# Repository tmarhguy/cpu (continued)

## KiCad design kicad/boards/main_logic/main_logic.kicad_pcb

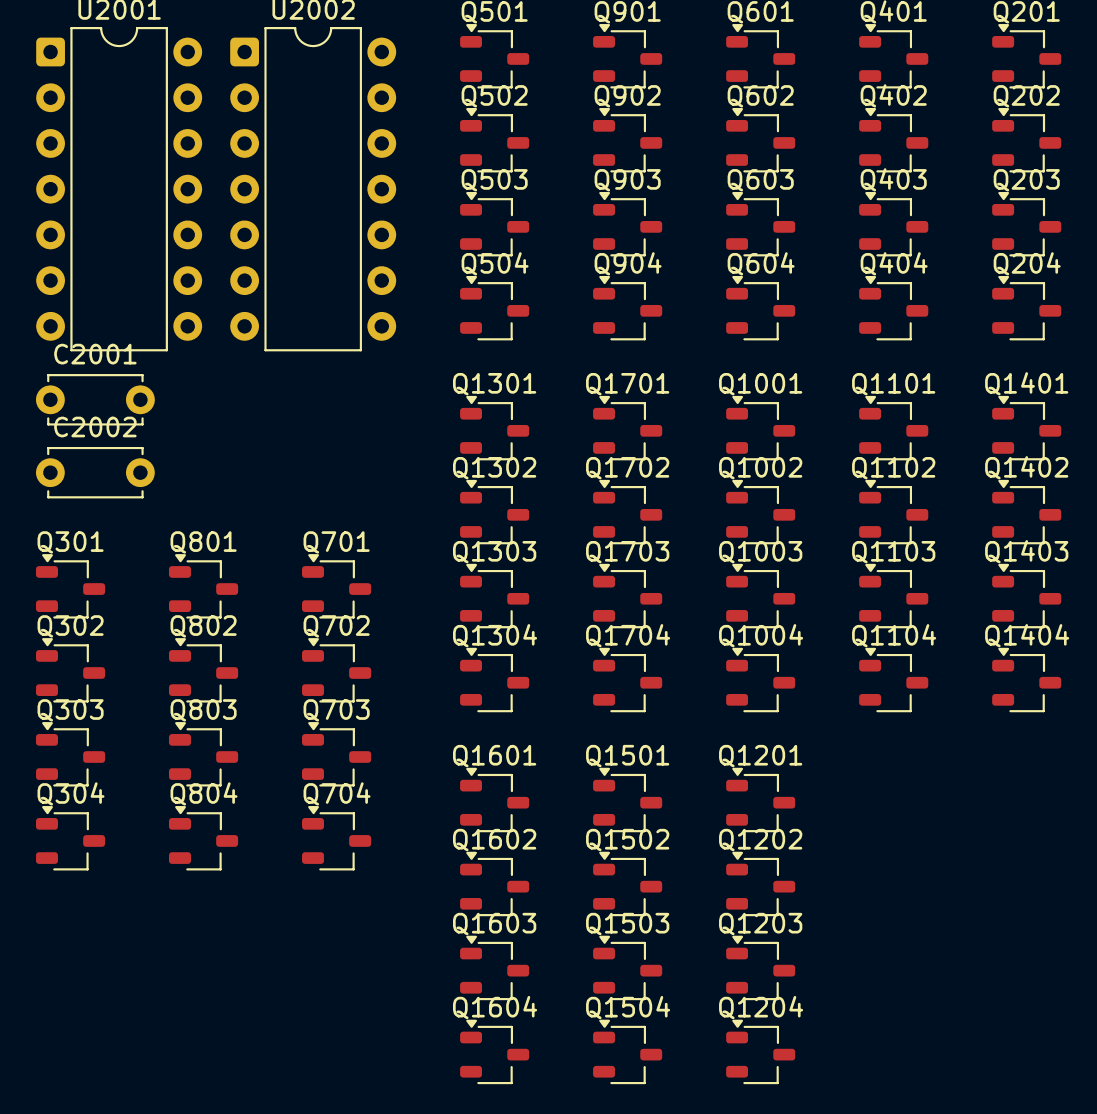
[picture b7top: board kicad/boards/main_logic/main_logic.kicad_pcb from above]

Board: 2 copper layers, 68 parts (0 on the bottom side), 66 nets, no tracks yet.

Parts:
C2001, C2002: 100nF; C_Disc_D5.0mm_W2.5mm_P5.00mm
Q201, Q204, Q301, Q304, Q401, Q404, Q501, Q504, Q601, Q604, Q701, Q704, Q801, Q804, Q901, Q904, Q1002, Q1003, Q1102, Q1103, Q1202, Q1203, Q1302, Q1303, Q1402, Q1403, Q1502, Q1503, Q1602, Q1603, Q1702, Q1703: PMOS; TSOT-23
Q202, Q203, Q302, Q303, Q402, Q403, Q502, Q503, Q602, Q603, Q702, Q703, Q802, Q803, Q902, Q903, Q1001, Q1004, Q1101, Q1104, Q1201, Q1204, Q1301, Q1304, Q1401, Q1404, Q1501, Q1504, Q1601, Q1604, Q1701, Q1704: NMOS; TSOT-23
U2001, U2002: 74HC86; DIP-14_W7.62mm

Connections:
/nand8_1/A0: Q201.2 (G), Q203.2 (G)
/nand8_1/A1: Q301.2 (G), Q303.2 (G)
/nand8_1/A2: Q401.2 (G), Q403.2 (G)
/nand8_1/A3: Q501.2 (G), Q503.2 (G)
/nand8_1/A4: Q601.2 (G), Q603.2 (G)
/nand8_1/A5: Q701.2 (G), Q703.2 (G)
/nand8_1/A6: Q801.2 (G), Q803.2 (G)
/nand8_1/A7: Q901.2 (G), Q903.2 (G)
/nand8_1/B0: Q202.2 (G), Q204.2 (G)
/nand8_1/B1: Q302.2 (G), Q304.2 (G)
/nand8_1/B2: Q402.2 (G), Q404.2 (G)
/nand8_1/B3: Q502.2 (G), Q504.2 (G)
/nand8_1/B4: Q602.2 (G), Q604.2 (G)
/nand8_1/B5: Q702.2 (G), Q704.2 (G)
/nand8_1/B6: Q802.2 (G), Q804.2 (G)
/nand8_1/B7: Q902.2 (G), Q904.2 (G)
/nand8_1/Y0: Q201.1 (D), Q202.1 (D), Q204.1 (D)
/nand8_1/Y1: Q301.1 (D), Q302.1 (D), Q304.1 (D)
/nand8_1/Y2: Q401.1 (D), Q402.1 (D), Q404.1 (D)
/nand8_1/Y3: Q501.1 (D), Q502.1 (D), Q504.1 (D)
/nand8_1/Y4: Q601.1 (D), Q602.1 (D), Q604.1 (D)
/nand8_1/Y5: Q701.1 (D), Q702.1 (D), Q704.1 (D)
/nand8_1/Y6: Q801.1 (D), Q802.1 (D), Q804.1 (D)
/nand8_1/Y7: Q901.1 (D), Q902.1 (D), Q904.1 (D)
/nor8_1/A0: Q1001.2 (G), Q1002.2 (G)
/nor8_1/A1: Q1101.2 (G), Q1102.2 (G)
/nor8_1/A2: Q1201.2 (G), Q1202.2 (G)
/nor8_1/A3: Q1301.2 (G), Q1302.2 (G)
/nor8_1/A4: Q1401.2 (G), Q1402.2 (G)
/nor8_1/A5: Q1501.2 (G), Q1502.2 (G)
/nor8_1/A6: Q1601.2 (G), Q1602.2 (G)
/nor8_1/A7: Q1701.2 (G), Q1702.2 (G)
/nor8_1/B0: Q1003.2 (G), Q1004.2 (G)
/nor8_1/B1: Q1103.2 (G), Q1104.2 (G)
/nor8_1/B2: Q1203.2 (G), Q1204.2 (G)
/nor8_1/B3: Q1303.2 (G), Q1304.2 (G)
/nor8_1/B4: Q1403.2 (G), Q1404.2 (G)
/nor8_1/B5: Q1503.2 (G), Q1504.2 (G)
/nor8_1/B6: Q1603.2 (G), Q1604.2 (G)
/nor8_1/B7: Q1703.2 (G), Q1704.2 (G)
/nor8_1/Y0: Q1001.1 (D), Q1003.1 (D), Q1004.1 (D)
/nor8_1/Y1: Q1101.1 (D), Q1103.1 (D), Q1104.1 (D)
/nor8_1/Y2: Q1201.1 (D), Q1203.1 (D), Q1204.1 (D)
/nor8_1/Y3: Q1301.1 (D), Q1303.1 (D), Q1304.1 (D)
/nor8_1/Y4: Q1401.1 (D), Q1403.1 (D), Q1404.1 (D)
/nor8_1/Y5: Q1501.1 (D), Q1503.1 (D), Q1504.1 (D)
/nor8_1/Y6: Q1601.1 (D), Q1603.1 (D), Q1604.1 (D)
/nor8_1/Y7: Q1701.1 (D), Q1703.1 (D), Q1704.1 (D)
GND: C2001.2, C2002.2, Q203.3 (S), Q303.3 (S), Q403.3 (S), Q503.3 (S), Q603.3 (S), Q703.3 (S), Q803.3 (S), Q903.3 (S), Q1001.3 (S), Q1004.3 (S), Q1101.3 (S), Q1104.3 (S), Q1201.3 (S), Q1204.3 (S), Q1301.3 (S), Q1304.3 (S), Q1401.3 (S), Q1404.3 (S), Q1501.3 (S), Q1504.3 (S), Q1601.3 (S), Q1604.3 (S), Q1701.3 (S), Q1704.3 (S), U2001.7 (GND), U2002.7 (GND)
unnamed: Q202.3 (S), Q203.1 (D)
unnamed: Q302.3 (S), Q303.1 (D)
unnamed: Q402.3 (S), Q403.1 (D)
unnamed: Q502.3 (S), Q503.1 (D)
unnamed: Q602.3 (S), Q603.1 (D)
unnamed: Q702.3 (S), Q703.1 (D)
unnamed: Q802.3 (S), Q803.1 (D)
unnamed: Q902.3 (S), Q903.1 (D)
unnamed: Q1002.1 (D), Q1003.3 (S)
unnamed: Q1102.1 (D), Q1103.3 (S)
unnamed: Q1202.1 (D), Q1203.3 (S)
unnamed: Q1302.1 (D), Q1303.3 (S)
unnamed: Q1402.1 (D), Q1403.3 (S)
unnamed: Q1502.1 (D), Q1503.3 (S)
unnamed: Q1602.1 (D), Q1603.3 (S)
unnamed: Q1702.1 (D), Q1703.3 (S)
VCC: C2001.1, C2002.1, Q201.3 (S), Q204.3 (S), Q301.3 (S), Q304.3 (S), Q401.3 (S), Q404.3 (S), Q501.3 (S), Q504.3 (S), Q601.3 (S), Q604.3 (S), Q701.3 (S), Q704.3 (S), Q801.3 (S), Q804.3 (S), Q901.3 (S), Q904.3 (S), Q1002.3 (S), Q1102.3 (S), Q1202.3 (S), Q1302.3 (S), Q1402.3 (S), Q1502.3 (S), Q1602.3 (S), Q1702.3 (S), U2001.14 (VCC), U2002.14 (VCC)

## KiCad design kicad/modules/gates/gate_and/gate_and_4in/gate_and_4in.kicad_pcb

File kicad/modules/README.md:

# KiCad Modules

This directory contains individual circuit modules organized by component type and specifications.

## Directory Structure

The modules are organized to match the component inventory requirements:

### Gate Modules

#### AND Gates
- `gate_and/gate_and_2in/` - 2-input, 1-bit AND gates (10× used in ALU)
- `gate_and/gate_and_3in/` - 3-input, 1-bit AND gates (1× used in ALU)
- `gate_and/gate_and_4in/` - 4-input, 1-bit AND gates (19× used in ALU - most common)
- `gate_and_8bit/` - 8-bit wide AND gates (legacy/alternative)

#### OR Gates
- `gate_or/gate_or_2in/` - 2-input, 1-bit OR gates (7× used in ALU)
- `gate_or/gate_or_3in/` - 3-input, 1-bit OR gates (1× used in ALU)
- `gate_or_8bit/` - 8-bit wide OR gates (legacy/alternative)

#### NOT Gates (Inverters)
- `gate_inv/gate_inv_1bit/` - 1-bit inverters (40× used in ALU)
- `gate_inv/gate_inv_8bit/` - 8-bit wide inverters (1× used in ALU)

#### NAND Gates
- `gate_nand/gate_nand_2in_8bit/` - 2-input, 8-bit NAND (1× used in ALU)
- `gate_nand/` - Legacy NAND gates

#### NOR Gates
- `gate_nor/gate_nor_2in_1bit/` - 2-input, 1-bit NOR (1× used in ALU)
- `gate_nor/gate_nor_2in_8bit/` - 2-input, 8-bit NOR (1× used in ALU)
- `gate_nor/gate_nor_8in_1bit/` - 8-input, 1-bit NOR for zero detection (1× used in ALU)
- `gate_nor_8bit/` - Legacy NOR gates

#### XOR Gates
- `gate_xor/gate_xor_2in_8bit/` - 2-input, 8-bit XOR (3× used in ALU)
- `gate_xor/` - Legacy XOR gates
- `gate_xor_8bit/` - Alternative 8-bit XOR
- `gate_xor_ic/` - XOR implemented as IC (74HC86)

#### XNOR Gates
- `gate_xnor/` - XNOR gate modules

### Multiplexers

#### MUX Modules
- `mux/mux_2to1_8bit/` - 2:1 MUX, 1-bit select, 8-bit data (2× used in ALU)
- `mux/mux_4to1_8bit/` - 4:1 MUX, 2-bit select, 8-bit data (3× used in ALU)
- `mux/mux_8to1_8bit/` - 8:1 MUX, 3-bit select, 8-bit data (1× used in ALU)
- `mux_8bit/` - Legacy multiplexer modules

### Arithmetic Modules

- `adder1/` - Single-bit full adder
- `adder2/` - 2-bit full adder
- `adder8/` - 8-bit full adder

### ALU Core

- `alu_core/` - ALU core module integration

## Usage Notes

1. **Primary Modules:** Use the organized subdirectories (e.g., `gate_and/gate_and_4in/`) for new designs matching the component inventory.

2. **Legacy Modules:** The root-level directories (e.g., `gate_and/`, `gate_or_8bit/`) contain existing designs and are preserved for compatibility.

3. **Component Sizes:** The organization matches the exact component sizes used in the ALU top circuit as documented in `docs/build-notes/component_inventory.md`.

4. **File Naming:** Each module directory should contain:
   - `.kicad_sch` - Schematic file
   - `.kicad_pcb` - PCB layout file
   - `.kicad_pro` - Project file
   - Backup subdirectories
   - Related documentation

## Migration Notes

When organizing existing designs:
- Move 2-input AND gates → `gate_and/gate_and_2in/`
- Move 3-input AND gates → `gate_and/gate_and_3in/`
- Move 4-input AND gates → `gate_and/gate_and_4in/`
- Move 2-input OR gates → `gate_or/gate_or_2in/`
- Move 3-input OR gates → `gate_or/gate_or_3in/`
- Move 1-bit inverters → `gate_inv/gate_inv_1bit/`
- Move 8-bit inverters → `gate_inv/gate_inv_8bit/`
- Move multiplexers by size → `mux/mux_*to1_8bit/`

---

*Last updated: 2026-01-08*

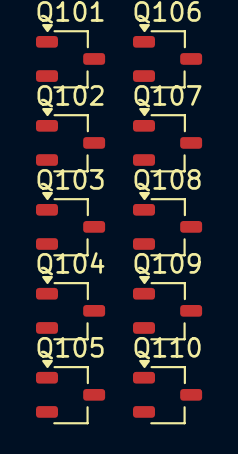
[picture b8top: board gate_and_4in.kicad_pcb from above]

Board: 2 copper layers, 10 parts (0 on the bottom side), 11 nets, no tracks yet.

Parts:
Q101, Q106, Q107, Q108, Q109: PMOS; TSOT-23
Q102, Q103, Q104, Q105, Q110: NMOS; TSOT-23

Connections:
/A: Q101.2 (G), Q103.2 (G)
/B: Q102.2 (G), Q106.2 (G)
/C: Q104.2 (G), Q107.2 (G)
/D: Q105.2 (G), Q108.2 (G)
/Y: Q109.1 (D), Q110.1 (D)
GND: Q105.3 (S), Q110.3 (S)
unnamed: Q101.1 (D), Q102.1 (D), Q106.1 (D), Q107.1 (D), Q108.1 (D), Q109.2 (G), Q110.2 (G)
unnamed: Q102.3 (S), Q103.1 (D)
unnamed: Q103.3 (S), Q104.1 (D)
unnamed: Q104.3 (S), Q105.1 (D)
VCC: Q101.3 (S), Q106.3 (S), Q107.3 (S), Q108.3 (S), Q109.3 (S)

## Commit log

2025-07-21 chore: initial project scaffold
2025-11-13 Restructure project: remove old config files, add ALU design documentation
2025-11-13 docs: add professional README files and project story
    - Add comprehensive main README with professional formatting
    - Add story behind the project (CS vs CompE debate)
    - Create professional README files for all directories:
    - hardware/README.md with ALU architecture details
    - schematics/README.md with circuit designs
    - tests/README.md with test vector information
2025-11-13 docs: update README with simplified structure and fix navigation
    - Simplify README structure while maintaining professional format
    - Fix navigation links and anchor references
    - Update badges layout for better readability
    - Remove redundant content while preserving key information
2025-11-13 docs: restore complete README with proper formatting and all sections
    - Restore full README content with all sections
    - Fix badge formatting for proper GitHub rendering
    - Update story text to match project description
    - Ensure all navigation links work correctly
    - Complete documentation with architecture, components, and skills
2025-11-13 Consolidate badge links in README.md
    Removed redundant badge links and consolidated them for clarity.
2025-11-13 Restore order
    reorganized sections
2025-11-13 docs: update architecture diagram with complete system block diagram
    - Replace simplified diagram with detailed complete system architecture
    - Add 5 stages of architecture breakdown
    - Include ALU core architecture details
    - Show full data flow from input to display
2025-11-13 docs: fix horizontal scrollbar by making architecture diagram more compact
2025-11-14 docs: add input system encoder design rationale and implementation notes
    - Add 26-key to 5-bit encoder design documentation
    - Document three encoding options with transistor cost analysis
    - Explain recommended zero-transistor solutions (diode matrix and Arduino scanning)
    - Justify avoiding CMOS logic encoder (200-400 transistors)
    - Align with project philosophy of transistor minimization
2025-11-14 docs: enhance input system documentation with matrix keypad architecture details
    - Add 5×6 matrix keypad architecture specification
    - Document scanning method and key indexing strategy (row × 6 + column)
    - Clarify Arduino front-end responsibilities
    - Update recommended solution to focus on matrix scanning
    - Add advantages section highlighting benefits for CPU project
2026-01-07 ALU milestone — transistor-level gates to verified 8-bit operations
    Summary:
    Completed a major ALU milestone by designing, simulating, and integrating an 8-bit arithmetic-logic unit across three abstraction layers: transistor-level CMOS (ngspice), gate-level datapaths (Logisi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
    Transistor-level (ngspice / device physics):
    * Designed and verified custom CMOS logic gates (NOT, NAND, NOR, XOR) from discrete MOSFETs
    * Validated functionality, voltage levels, and switching behavior using ngspice simulations
2026-01-09 docs: add ALU architecture + ops spec; refactor KiCad hierarchy; finish adder/mux/LED subsystems
    * Reorganized and refactored entire KiCad project structure (clean hierarchy, reusable sheets/symbols, stabilized file dependencies)
    * Added dependent/composed gates (e.g., 3-input AND built from 2-input primitives) to reduce duplication and standardize building blocks
    * Completed arithmetic engine: half-adder/full-adder factorization -> integrated 8-bit adder backbone supporting ADD/SUB/INC/DEC/CMP via B invert + carry-in control
    * Built hierarchical mux fabric: 2->1 primitive -> 4->1 8-bit mux assembled from 2->1 (4-bit/bit-sliced) stages; standardized selection wiring for datapath output ro
2026-01-09 feat: complete circuit designs for all ALU components
    * Designed all gate modules: AND, OR, NOT, NAND, NOR, XOR (1-bit and 8-bit variants)
    * Completed multiplexer hierarchy: 2:1, 4:1, and 8:1 8-bit muxes
    * Finalized add_sub board schematic and LED panel designs
    * Added new board modules: flags, main_control, main_logic
    * Updated Logisim top-level ALU circuit
    * Note: KiCad directory path errors to be resolved next (iCloud sync issue), then begin PCB routing
2026-01-10 Fix KiCad file paths and complete core circuit design
    - Fixed file path errors across all KiCad schematics and projects
    - Completed core circuit designs:
    * Adder and subtractor modules (adder2, adder8)
    * LED panels (led_panel_1) with display circuits
    * Flag LED circuits for status indicators
    * All dependent logic gate modules (AND, OR, NOT, NAND, NOR, XOR)
2026-01-10 Document ALU control signals with detailed opcode table
    - Added complete opcode table with decimal and binary encodings
    - Documented all 19 operations with implementation details
    - Explained logic operations via inversion:
    * AND implemented as NAND + invert (INV_OUT=1)
    * OR implemented as NOR + invert (INV_OUT=1)
    * XNOR implemented as XOR + invert (INV_OUT=1)
2026-01-10 Add opcode table CSV to repository
    - Updated .gitignore to allow CSV files in spec/ directory
    - Added opcode_table.csv with decimal and binary encodings
    - CSV includes: OPCODE Decimal, Binary, FUNC[3:0], Operation, Description, Implementation details, Circuit Progress
2026-01-12 Add verification procedures documentation
2026-01-12 Add opcode implementation status documentation
2026-01-12 Add timing verification notes
2026-01-12 Add bring-up checklist documentation
2026-01-12 Add schematics documentation
2026-01-12 Add release packaging notes
2026-01-12 Add Arduino firmware and build notes
2026-01-12 ci: add validation workflow for test vectors
2026-01-12 Add ALU test vectors and validator
2026-01-12 Add JSON vector test runner
2026-01-12 ci: use clang-format for firmware checks
2026-01-14 Revise README
2026-01-16 Complete documentation restructure and verification system
    - Restructured documentation from 44+ files to 19 essential documents
    - Added comprehensive technical documentation
    - Integrated exhaustive test results (1,247,084 tests at 100%)
    - Consolidated results directory with simulation metrics
    - Updated specifications: 5-bit opcode, combinational, 270x270mm
    - Added complete author attribution
2026-01-16 Exclude large files from repository
    - Ignore test/vectors/exhaustive.json (314MB)
    - Ignore results/test_results.json (523MB)
    - Ignore large video files >100MB
    - Files remain locally but not tracked in git
2026-01-16 Add PUSH_READY.txt verification file
2026-01-16 Update .gitignore to exclude all large files
